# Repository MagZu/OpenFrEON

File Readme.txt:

The plan is to gradually promote adjustments:
1. Adjust the size of the buckle so that it can fit the gopro socket in the market. (Has been completed)
2. Add LeTV phone case. (During testing)
3. Adjust the structural defects of the mobile phone case. (under design)
4. Cancel the hardware. Use the wood structure to ensure the strength of the buckle. (To be started)

Shell introduction, hardware details and purchase link
http://www.openpilot.net/?thread-14.htm

In the folder
pedal
giraffe
leeco
oneplus
gopro
*old is officially owned by openfreon

All rights reserved by copyright owners

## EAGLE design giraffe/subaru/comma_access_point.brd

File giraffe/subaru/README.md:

Subaru giraffe
====

Get your panda deeper into your Subaru Impreza
May work with other cars with the same connector

====

All switching between stock ADAS on and Stock ADAS off is done via a relay

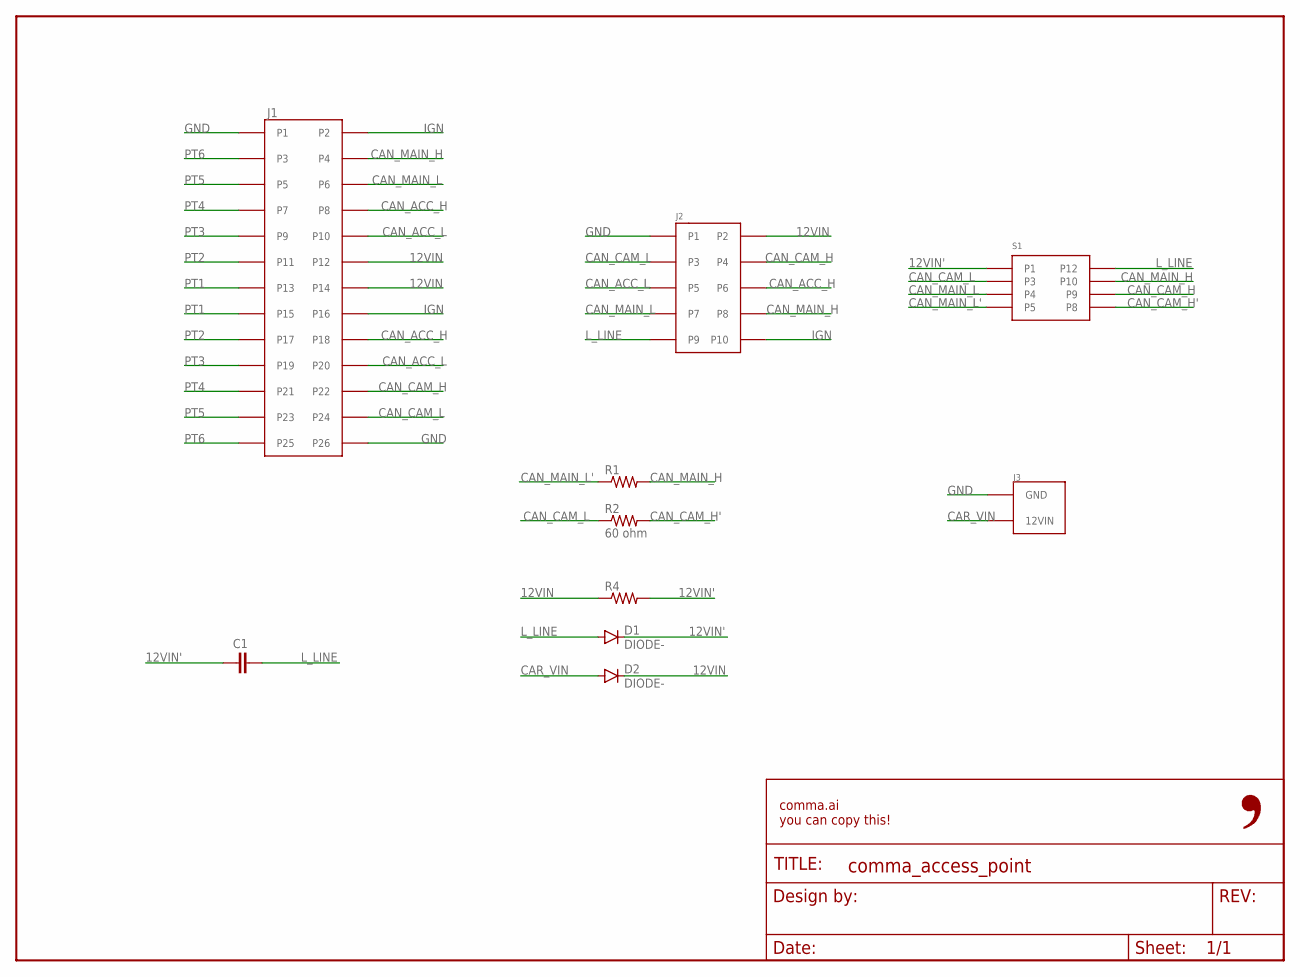
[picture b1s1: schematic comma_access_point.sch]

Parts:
C1: C0805; 0805-C
D1, D2: DIODE-; DO-214
FRAME1: FRAME-LETTER-OPENNO_PACKAGE; DUMMY
J1: 5018762640
J2: 5018761040
J3: 3-794618-2
R1, R4: R0402; 0402-R
R2: 60 ohm; 0402-R
S1: G6S-2G-DC12; G6S-26-DC12

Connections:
12VIN: D2.1 (C), J1.P12, J1.P14, J2.P2, R4.1
12VIN': C1.1, D1.1 (C), R4.2, S1.P1
CAN_ACC_H: J1.P8, J1.P18, J2.P6
CAN_ACC_L: J1.P10, J1.P20, J2.P5
CAN_CAM_H: J1.P22, J2.P4, S1.P9
CAN_CAM_H': R2.2, S1.P8
CAN_CAM_L: J1.P24, J2.P3, R2.1, S1.P3
CAN_MAIN_H: J1.P4, J2.P8, R1.2, S1.P10
CAN_MAIN_L: J1.P6, J2.P7, S1.P4
CAN_MAIN_L': R1.1, S1.P5
CAR_VIN: D2.2 (A), J3.12VIN
GND: J1.P1, J1.P26, J2.P1, J3.GND
IGN: J1.P2, J1.P16, J2.P10
L_LINE: C1.2, D1.2 (A), J2.P9, S1.P12
PT1: J1.P13, J1.P15
PT2: J1.P11, J1.P17
PT3: J1.P9, J1.P19
PT4: J1.P7, J1.P21
PT5: J1.P5, J1.P23
PT6: J1.P3, J1.P25

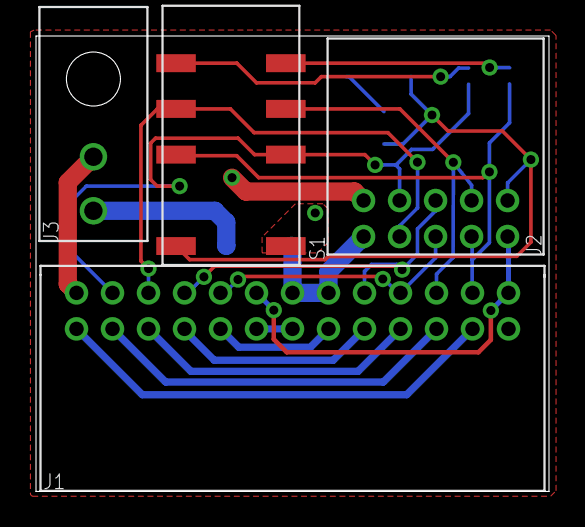
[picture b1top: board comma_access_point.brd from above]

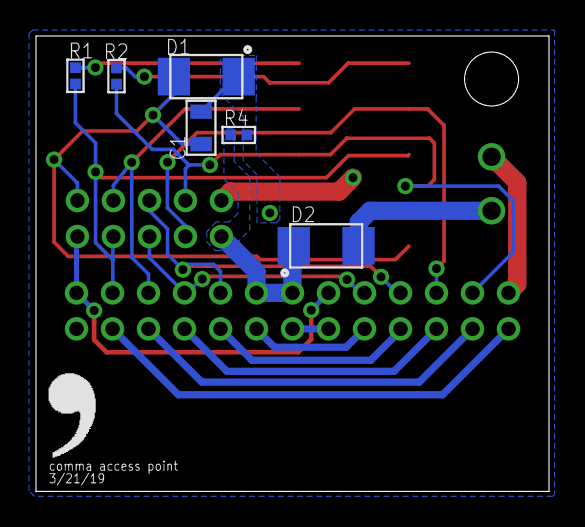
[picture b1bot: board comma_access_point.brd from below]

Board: 2 copper layers, 28.5 x 25.3 mm, 12 parts (7 on the bottom side), 20 nets.

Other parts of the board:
U$1: LOGO

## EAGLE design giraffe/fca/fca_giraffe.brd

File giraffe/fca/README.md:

FCA (Fiat Chrysler Automotive) Giraffe
====

Get your panda deeper into your:

- 2017 Chrysler Pacifica Hybrid

May fit other FCA cars as well.

The switches
====

The 2 DIP switches control signals to the stock ADAS system

- 1 -- IGN to camera

- 2 -- ADAS CAN1 -> camera CAN (OBDII pins 12 & 13)

Initial design from the community from: [@adhintz](https://github.com/adhintz)

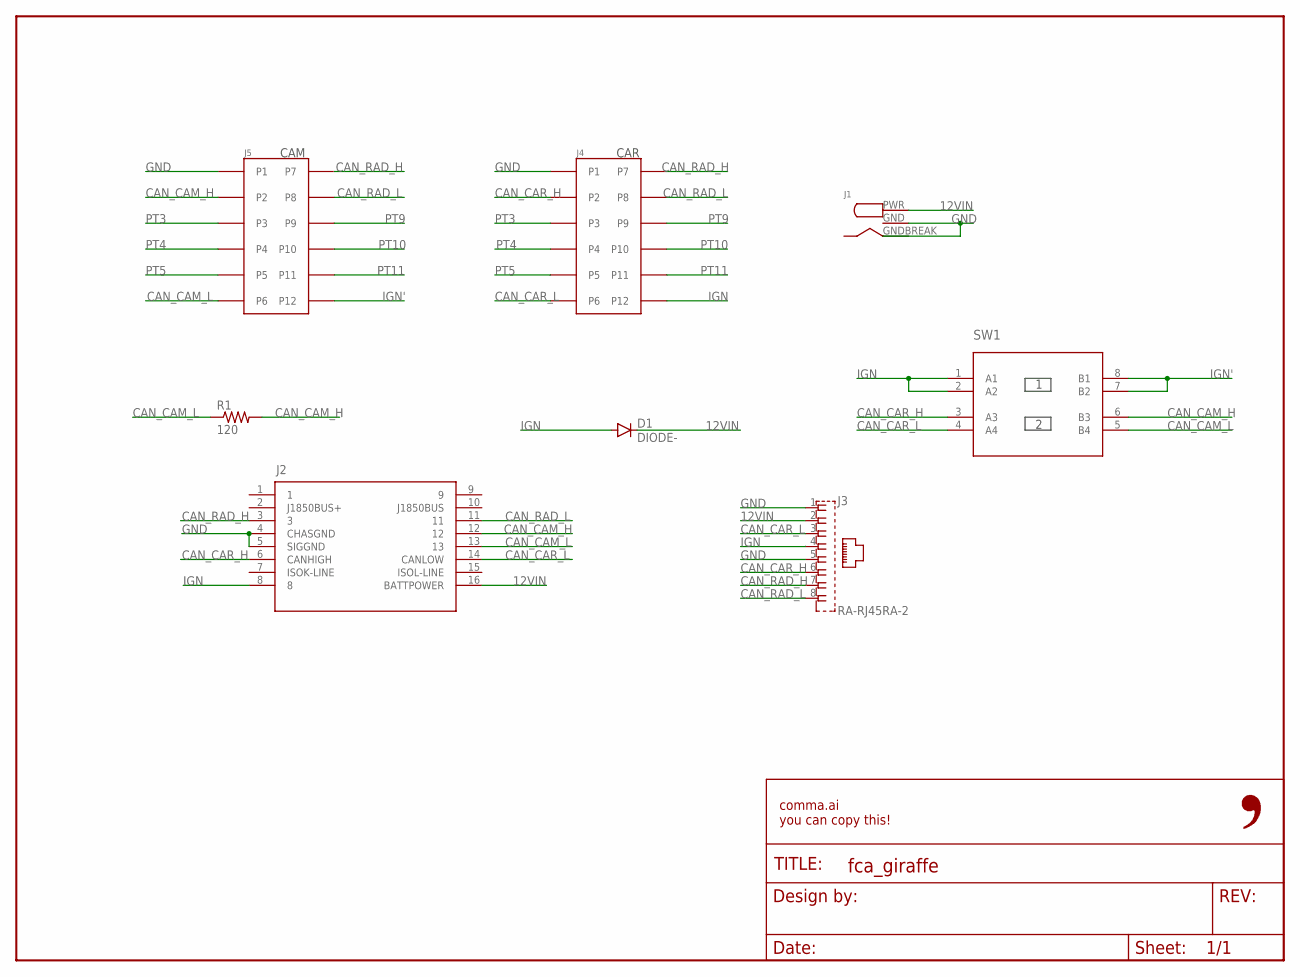
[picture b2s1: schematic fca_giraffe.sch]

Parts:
D1: DIODE-; DO-214
FRAME1: FRAME-LETTER-OPENNO_PACKAGE; DUMMY
J1: RASM722PX
J2: OBDII-FEMALE-CUT; OBDII-FEMALE-MIDCUT
J3: RA-RJ45RA-2; RA-RJ45-2
J4: 0348250124
J5: 0348240124
R1: 120; 0603-R
SW1: 2XDPST-CTS; 2-DPST

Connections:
12VIN: D1.1 (C), J1.PWR (12VIN), J2.16 (BATTPOWER), J3.2
CAN_CAM_H: J2.12, J5.P2, R1.2, SW1.6 (B3)
CAN_CAM_L: J2.13, J5.P6, R1.1, SW1.5 (B4)
CAN_CAR_H: J2.6 (CANHIGH), J3.6, J4.P2, SW1.3 (A3)
CAN_CAR_L: J2.14 (CANLOW), J3.3, J4.P6, SW1.4 (A4)
CAN_RAD_H: J2.3, J3.7, J4.P7, J5.P7
CAN_RAD_L: J2.11, J3.8, J4.P8, J5.P8
GND: J1.GND, J1.GNDBREAK, J2.4 (CHASGND), J2.5 (SIGGND), J3.1, J3.5, J4.P1, J5.P1
IGN: D1.2 (A), J2.8, J3.4, J4.P12, SW1.1 (A1), SW1.2 (A2)
IGN': J5.P12, SW1.7 (B2), SW1.8 (B1)
PT3: J4.P3, J5.P3
PT4: J4.P4, J5.P4
PT5: J4.P5, J5.P5
PT9: J4.P9, J5.P9
PT10: J4.P10, J5.P10
PT11: J4.P11, J5.P11

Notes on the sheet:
CAR
CAM

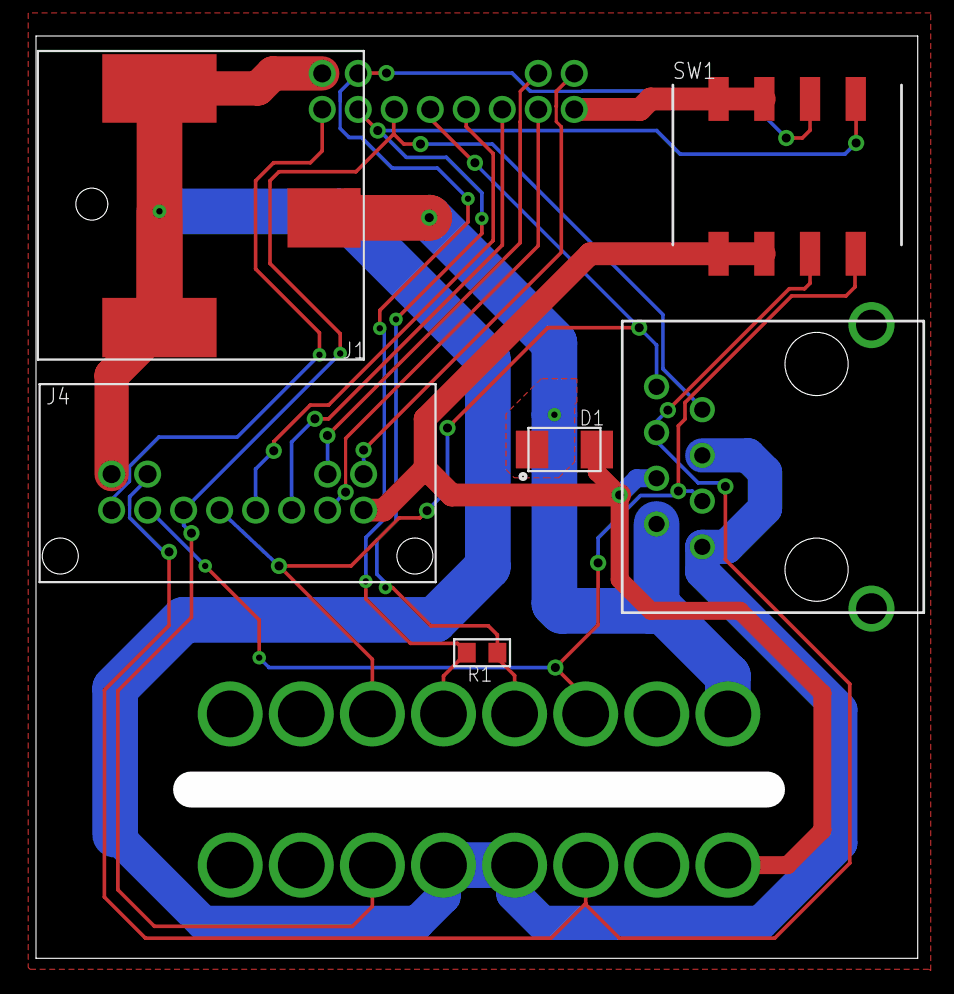
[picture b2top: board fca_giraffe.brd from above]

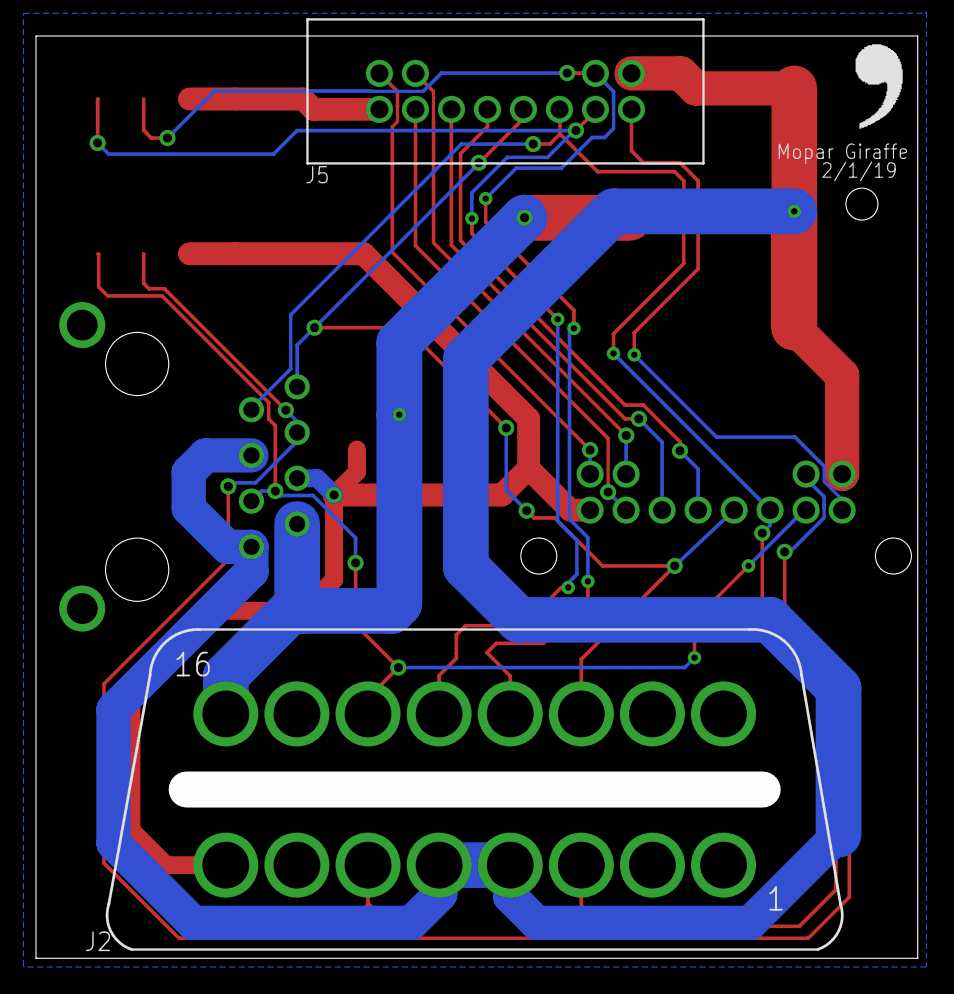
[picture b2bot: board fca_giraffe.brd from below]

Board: 2 copper layers, 49.0 x 51.2 mm, 10 parts (3 on the bottom side), 16 nets.

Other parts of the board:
U$1: LOGO

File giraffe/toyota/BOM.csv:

Ref Des,Package,Manufacturer PN,Qty,Link
J1,12-pin,1318774-1,1,http://www.mouser.com/Search/ProductDetail.aspx?R=1318774-1v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
J2,12-pin-RA,1318772-2,1,http://www.mouser.com/Search/ProductDetail.aspx?R=1318772-2v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
,,1123343-1,12,https://www.digikey.com/product-detail/en/te-connectivity-am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
,,PRPC040SAAN-RC,1,https://www.digikey.com/products/en?keywords=S1011EC-40-ND
J3,16-pin,OBDII-FEMALE,1,https://cn1514770021qfbj.en.alibaba.com/product/60598699808-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
J4,RJ45-RA,A-2004-2-4-LPS-N-R,1,https://www.digikey.com/product-detail/en/assmann-wsw-compon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
J5,3-pin,EJ508A,1,https://www.digikey.com/products/en?keywords=ej508a
SW1,SMD,204-214ST,1,https://www.digikey.com/scripts/DkSearch/dksus.dll?Detail&it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
R1,0603,ERJ-PA3F1200V,1,https://www.digikey.com/short/p47rhj
SCREWs,Phillips,92010A118,2,https://www.mcmaster.com/#catalog/92010A118

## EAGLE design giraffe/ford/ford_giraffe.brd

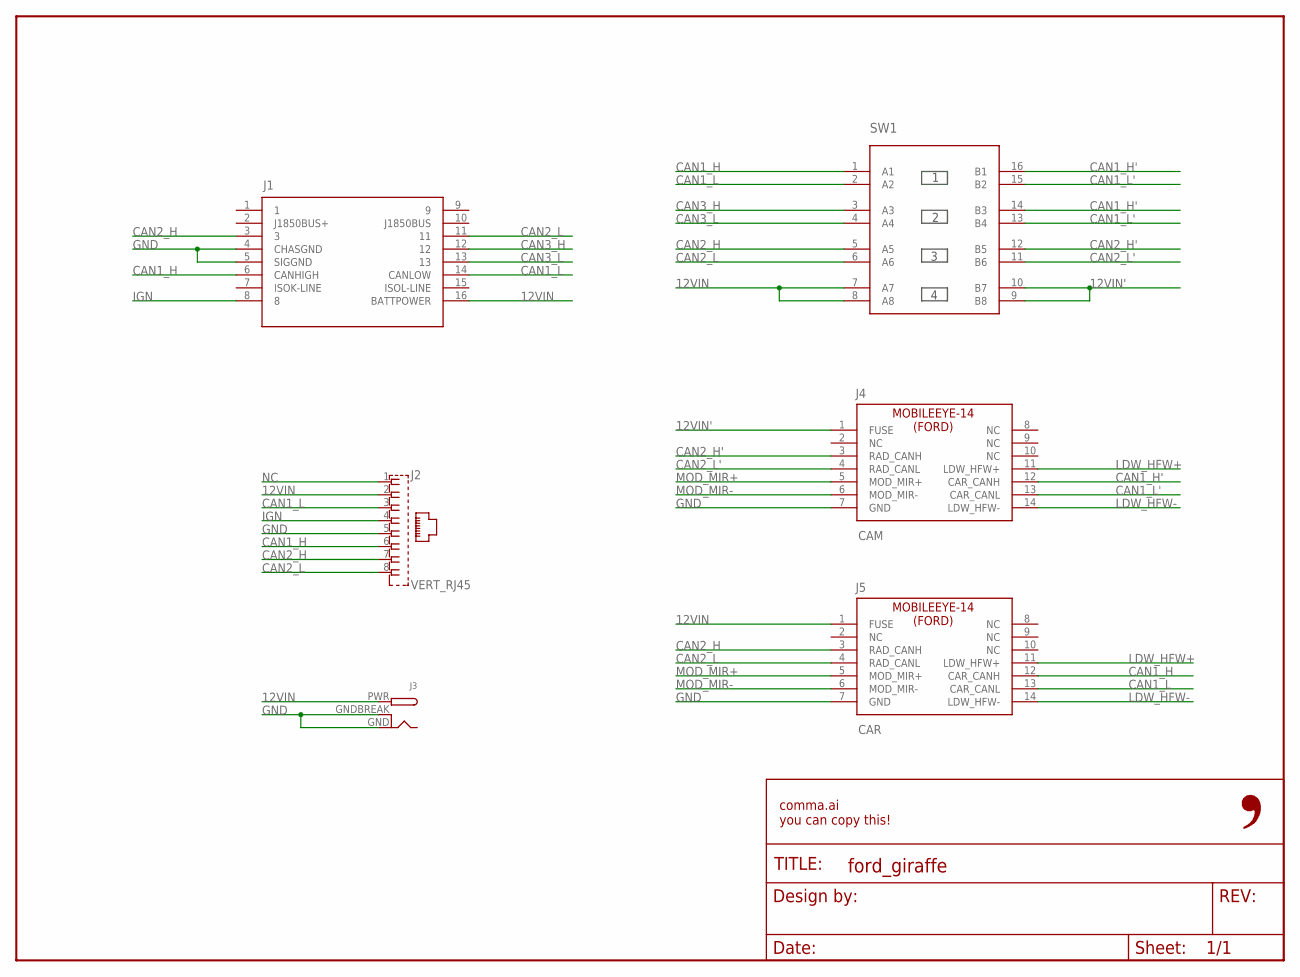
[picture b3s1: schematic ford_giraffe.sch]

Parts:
FRAME1: FRAME-LETTER-OPENNO_PACKAGE; DUMMY
J1: OBDII-FEMALE-CUT; OBDII-FEMALE-MIDCUT
J2: VERT_RJ45; GLX-S-88M
J3: DCBARRELPTH; DCJACK_2MM_PTH
J4: CAM; 2X7-FORD-CAR
J5: CAR; 2X7-FORD-CAM
SW1: 4XDPSTSMT; 4-DPST

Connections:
12VIN: J1.16 (BATTPOWER), J2.2, J3.PWR, J5.1 (FUSE), SW1.7 (A7), SW1.8 (A8)
12VIN': J4.1 (FUSE), SW1.9 (B8), SW1.10 (B7)
CAN1_H: J1.6 (CANHIGH), J2.6, J5.12 (CAR_CANH), SW1.1 (A1)
CAN1_H': J4.12 (CAR_CANH), SW1.14 (B3), SW1.16 (B1)
CAN1_L: J1.14 (CANLOW), J2.3, J5.13 (CAR_CANL), SW1.2 (A2)
CAN1_L': J4.13 (CAR_CANL), SW1.13 (B4), SW1.15 (B2)
CAN2_H: J1.3, J2.7, J5.3 (RAD_CANH), SW1.5 (A5)
CAN2_H': J4.3 (RAD_CANH), SW1.12 (B5)
CAN2_L: J1.11, J2.8, J5.4 (RAD_CANL), SW1.6 (A6)
CAN2_L': J4.4 (RAD_CANL), SW1.11 (B6)
CAN3_H: J1.12, SW1.3 (A3)
CAN3_L: J1.13, SW1.4 (A4)
GND: J1.4 (CHASGND), J1.5 (SIGGND), J2.5, J3.GND, J3.GNDBREAK, J4.7 (GND), J5.7 (GND)
IGN: J1.8, J2.4
LDW_HFW+: J4.11 (LDW_HFW+), J5.11 (LDW_HFW+)
LDW_HFW-: J4.14 (LDW_HFW-), J5.14 (LDW_HFW-)
MOD_MIR+: J4.5 (MOD_MIR+), J5.5 (MOD_MIR+)
MOD_MIR-: J4.6 (MOD_MIR-), J5.6 (MOD_MIR-)
NC: J2.1

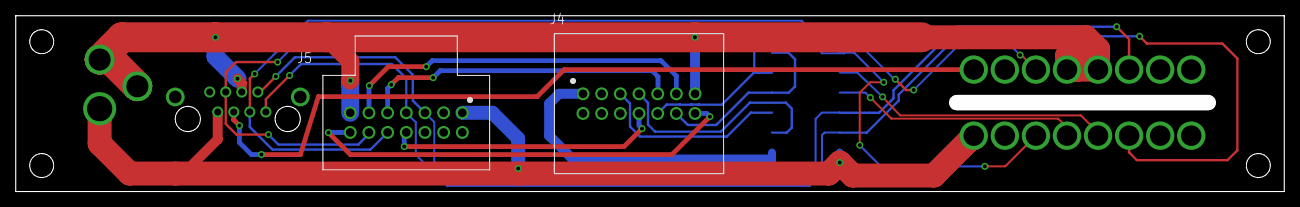
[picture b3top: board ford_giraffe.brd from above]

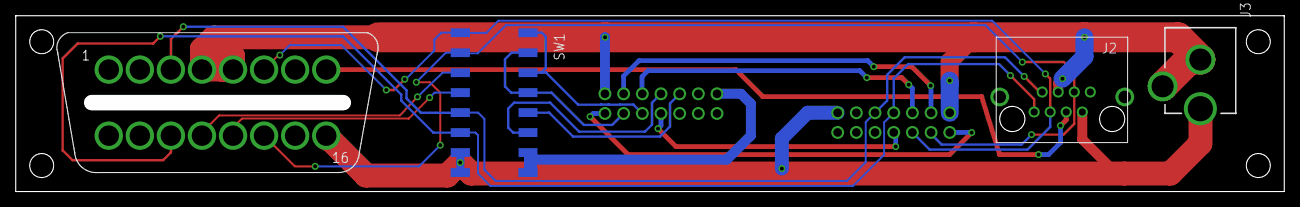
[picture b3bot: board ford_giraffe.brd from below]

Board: 2 copper layers, 161.3 x 22.4 mm, 7 parts (4 on the bottom side), 18 nets.

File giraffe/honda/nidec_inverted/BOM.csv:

Ref Des,Package,Manufacturer PN,Qty,Link
J1,20-pin-RA,MX34020NF1,1,https://www.digikey.com/product-detail/en/jae-electronics/MX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
J2,20-pin,MX34020SF1,1,https://www.digikey.com/scripts/DkSearch/dksus.dll?Detail&it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
,,M34S75C4F1,20,https://www.digikey.com/product-detail/en/jae-electronics/M3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
,,PRPC040SAAN-RC,1,https://www.digikey.com/products/en?keywords=S1011EC-40-ND
J3,16-pin,OBDII-FEMALE,1,https://cn1514770021qfbj.en.alibaba.com/product/60598699808-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
J4,RJ45-VERT,A-2014-2-4-LP/FS-R,1,https://www.digikey.com/scripts/DkSearch/dksus.dll?Detail&it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
SW1,SMD,204-214ST,1,https://www.digikey.com/scripts/DkSearch/dksus.dll?Detail&it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
SCREWs,Phillips,92010A118,2,https://www.mcmaster.com/#catalog/92010A118

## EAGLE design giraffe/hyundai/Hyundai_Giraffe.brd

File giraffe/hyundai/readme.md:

Hyundai giraffe
====

Get your panda deeper into your compatible Hyundai vehicle. Built with pinout for our Hyundai Sante Fe. May work with other Hyundai/Kia, check EWD for verification. 

The switches
====

The 4 DIP switches control signals to the stock ADAS system

- 1 -- ADAS CAN1 -> main body CAN

- 2 -- ADAS CAN1 -> panda CAN3 (OBDII pins 12 & 13)

- 3 -- IGNITION POWER -> panda power

- 4 -- ADAS power & ignition -> power & ignition

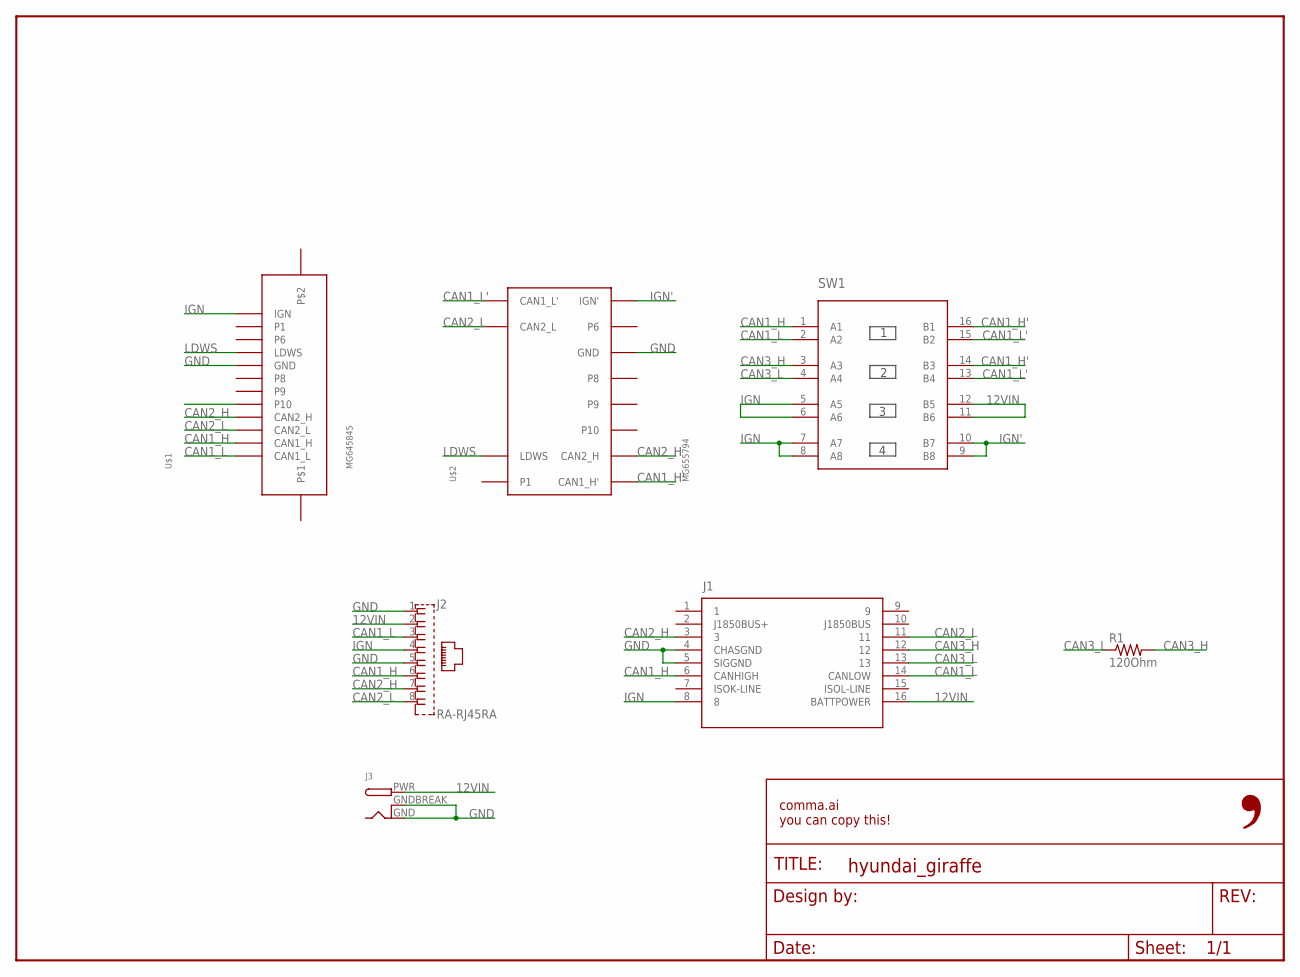
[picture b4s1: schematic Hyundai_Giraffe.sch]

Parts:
FRAME1: FRAME-LETTER-OPENNO_PACKAGE; DUMMY
J1: OBDII-FEMALE-CUT; OBDII-FEMALE-MIDCUT
J2: RA-RJ45RA; RA-RJ45
J3: DCBARRELPTH; DCJACK_2MM_PTH
R1: 120Ohm; 0603-R
SW1: 4XDPSTSMT; 4-DPST
U$1: MG645845
U$2: MG655794

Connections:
12VIN: J1.16 (BATTPOWER), J2.2, J3.PWR, SW1.11 (B6), SW1.12 (B5)
CAN1_H: J1.6 (CANHIGH), J2.6, SW1.1 (A1), U$1.CAN1_H
CAN1_H': SW1.14 (B3), SW1.16 (B1), U$2.CAN1_H'
CAN1_L: J1.14 (CANLOW), J2.3, SW1.2 (A2), U$1.CAN1_L
CAN1_L': SW1.13 (B4), SW1.15 (B2), U$2.CAN1_L'
CAN2_H: J1.3, J2.7, U$1.CAN2_H, U$2.CAN2_H
CAN2_L: J1.11, J2.8, U$1.CAN2_L, U$2.CAN2_L
CAN3_H: J1.12, R1.2, SW1.3 (A3)
CAN3_L: J1.13, R1.1, SW1.4 (A4)
GND: J1.4 (CHASGND), J1.5 (SIGGND), J2.1, J2.5, J3.GND, J3.GNDBREAK, U$1.GND, U$2.GND
IGN: J1.8, J2.4, SW1.5 (A5), SW1.6 (A6), SW1.7 (A7), SW1.8 (A8), U$1.IGN
IGN': SW1.9 (B8), SW1.10 (B7), U$2.IGN'
LDWS: U$1.LDWS, U$2.LDWS

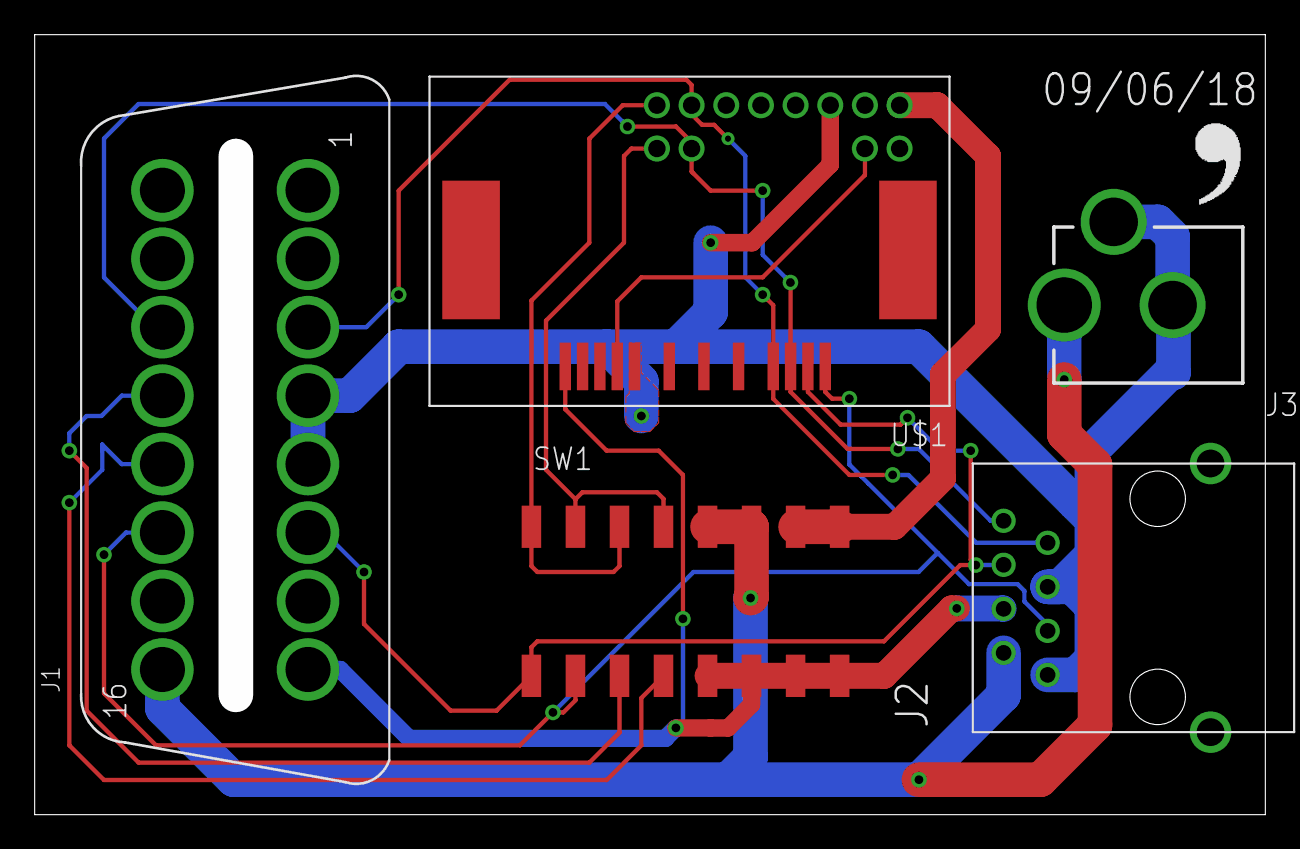
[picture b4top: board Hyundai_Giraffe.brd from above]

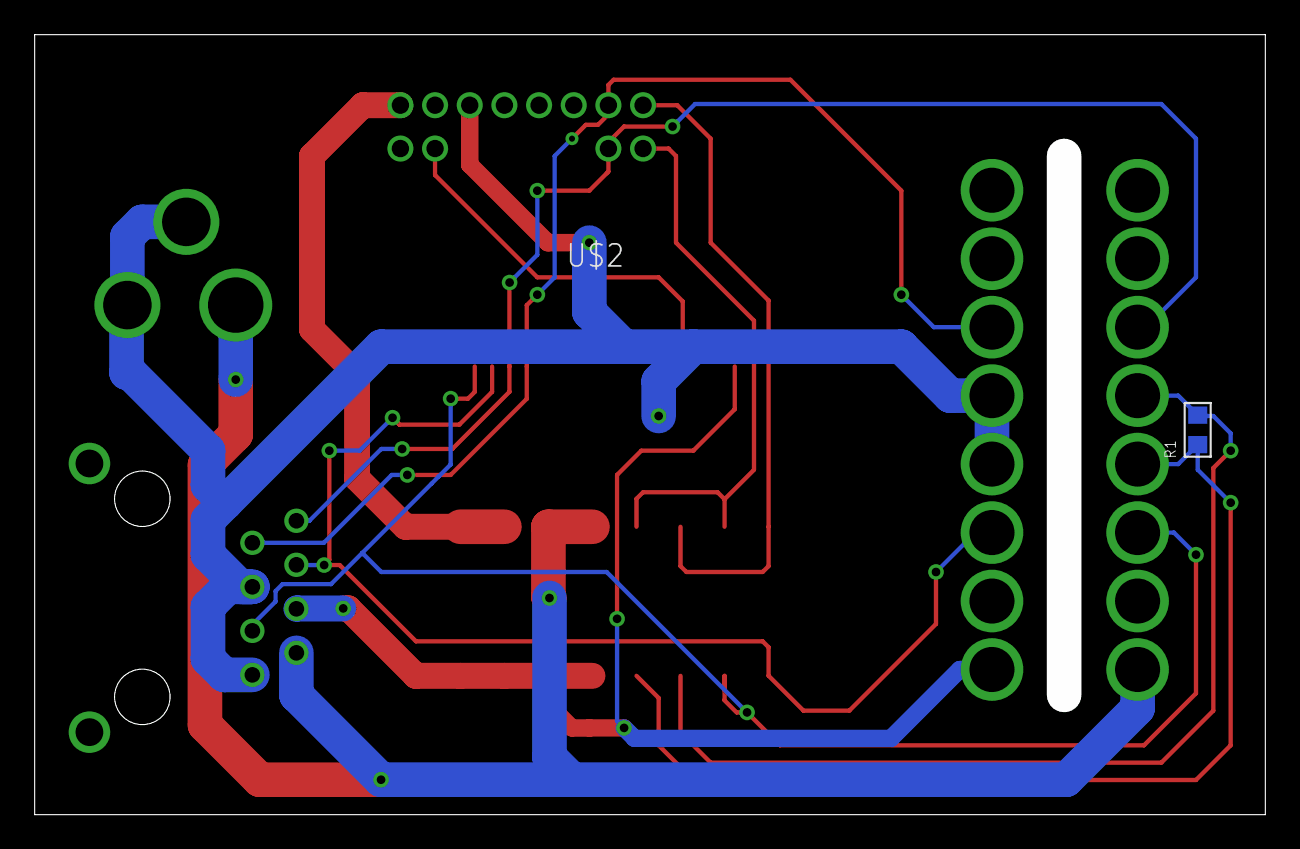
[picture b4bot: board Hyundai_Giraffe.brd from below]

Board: 2 copper layers, 71.0 x 45.0 mm, 9 parts (2 on the bottom side), 13 nets.

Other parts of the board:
U$3: LOGO

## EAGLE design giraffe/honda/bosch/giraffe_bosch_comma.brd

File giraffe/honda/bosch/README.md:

Honda giraffe (Bosch ADAS)
====

Get your panda deeper into your:

- 2017+ Honda CR-V
- 2017+ Honda Civic Hatchback
- 2018+ Honda Accord

May fit other Hondas with Bosch hardware as well.

The switches
====

The 2 DIP switches control signals to the stock ADAS system

- 1 -- IGN to camera

- 2 -- ADAS CAN2 -> camera CAN (OBDII pins 12 & 13)

Initial design from the community from: [@csouers](https://github.com/csouers), [@energee](https://github.com/energee), and Alaric Egli

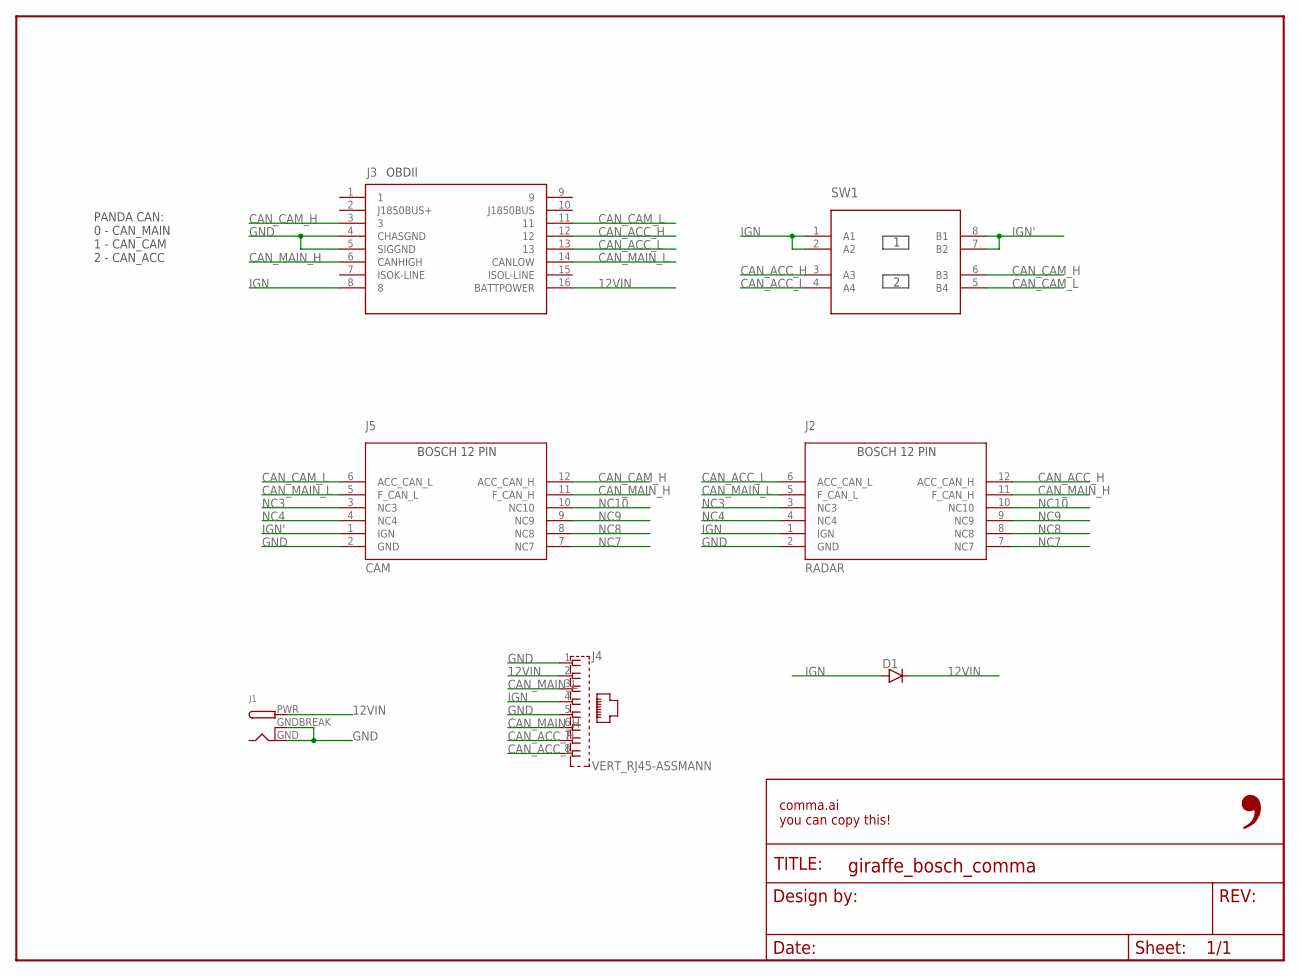
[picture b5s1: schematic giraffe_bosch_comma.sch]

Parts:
D1: DIODE-; DO-214
FRAME1: FRAME-LETTER-OPENNO_PACKAGE; DUMMY
J1: DCBARRELPTH; DCJACK_2MM_PTH
J2: RADAR; BOSCH_12_PIN_FEMALE
J3: OBDII-FEMALE-CUT; OBDII-FEMALE-MIDCUT
J4: VERT_RJ45-ASSMANN; RJ45-VERT
J5: CAM; BOSCH_12_PIN_MALE
SW1: 2XDPST-CTS; 2-DPST

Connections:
12VIN: D1.1 (C), J1.PWR, J3.16 (BATTPOWER), J4.2
CAN_ACC_H: J2.12 (ACC_CAN_H), J3.12, J4.7, SW1.3 (A3)
CAN_ACC_L: J2.6 (ACC_CAN_L), J3.13, J4.8, SW1.4 (A4)
CAN_CAM_H: J3.3, J5.12 (ACC_CAN_H), SW1.6 (B3)
CAN_CAM_L: J3.11, J5.6 (ACC_CAN_L), SW1.5 (B4)
CAN_MAIN_H: J2.11 (F_CAN_H), J3.6 (CANHIGH), J4.6, J5.11 (F_CAN_H)
CAN_MAIN_L: J2.5 (F_CAN_L), J3.14 (CANLOW), J4.3, J5.5 (F_CAN_L)
GND: J1.GND, J1.GNDBREAK, J2.2 (GND), J3.4 (CHASGND), J3.5 (SIGGND), J4.1, J4.5, J5.2 (GND)
IGN: D1.2 (A), J2.1 (IGN), J3.8, J4.4, SW1.1 (A1), SW1.2 (A2)
IGN': J5.1 (IGN), SW1.7 (B2), SW1.8 (B1)
NC3: J2.3 (NC3), J5.3 (NC3)
NC4: J2.4 (NC4), J5.4 (NC4)
NC7: J2.7 (NC7), J5.7 (NC7)
NC8: J2.8 (NC8), J5.8 (NC8)
NC9: J2.9 (NC9), J5.9 (NC9)
NC10: J2.10 (NC10), J5.10 (NC10)

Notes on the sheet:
OBDII
PANDA CAN: 0 - CAN_MAIN 1 - CAN_CAM 2 - CAN_ACC

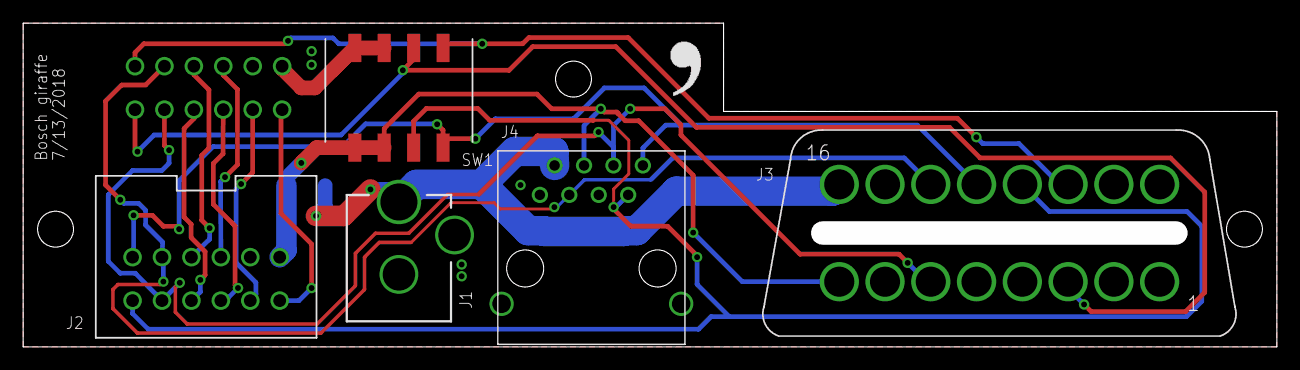
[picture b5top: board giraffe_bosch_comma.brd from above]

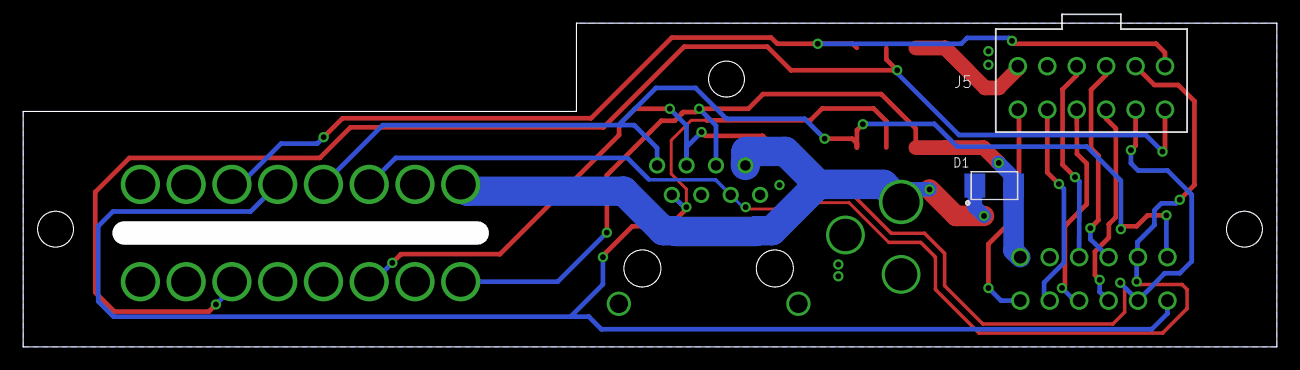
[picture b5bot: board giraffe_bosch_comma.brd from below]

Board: 2 copper layers, 108.2 x 27.9 mm, 9 parts (2 on the bottom side), 16 nets.

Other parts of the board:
U$1: LOGO

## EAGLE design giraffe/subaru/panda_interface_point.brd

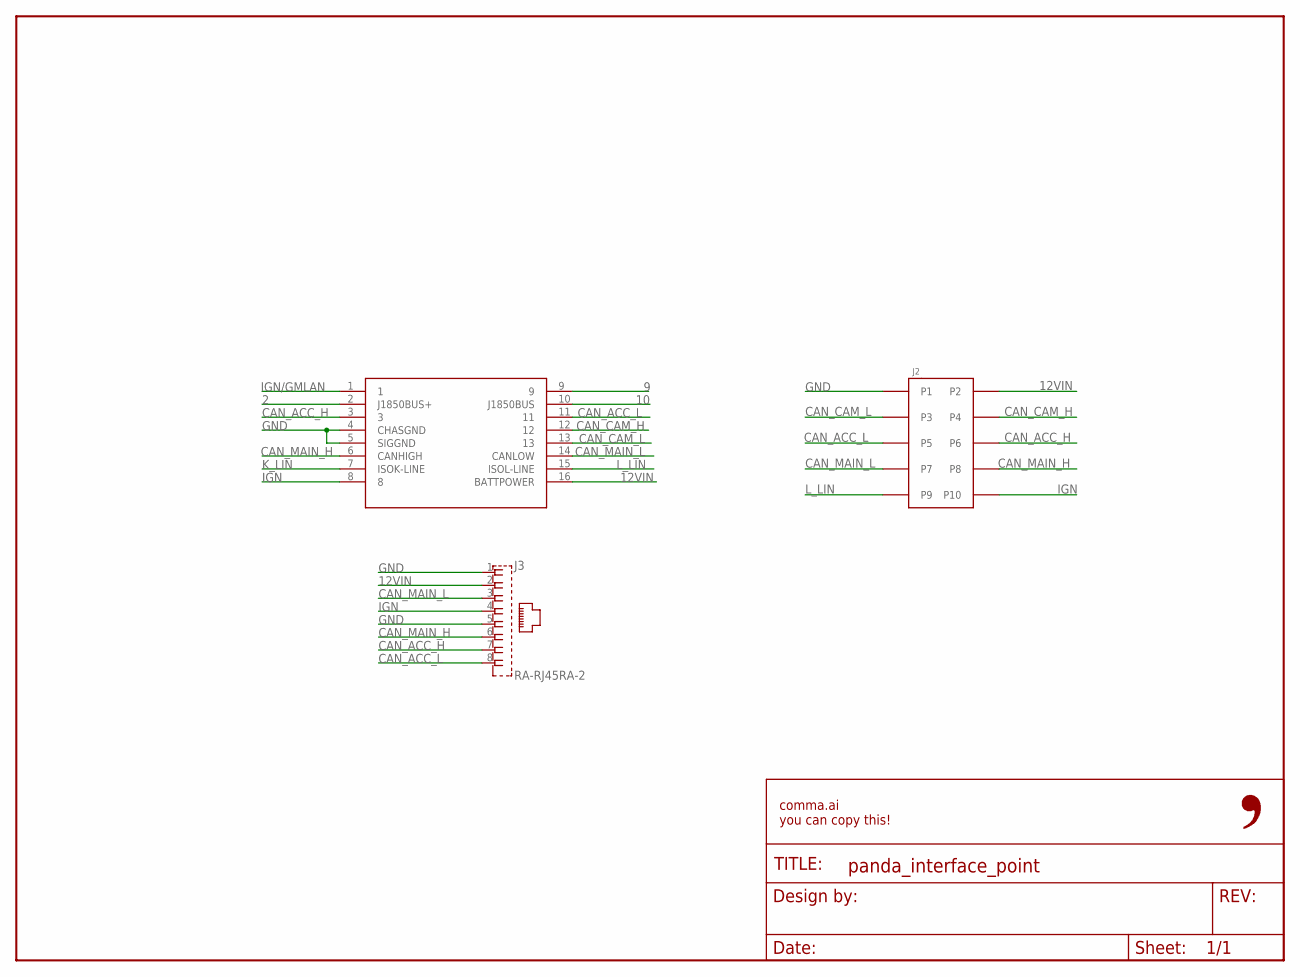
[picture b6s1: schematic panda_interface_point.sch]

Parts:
FRAME1: FRAME-LETTER-OPENNO_PACKAGE; DUMMY
J1: OBDII-FEMALE-CUT; OBDII-FEMALE-MIDCUT
J2: 5018761040
J3: RA-RJ45RA-2; RA-RJ45-2

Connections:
2: J1.2 (J1850BUS+)
9: J1.9
10: J1.10 (J1850BUS)
12VIN: J1.16 (BATTPOWER), J2.P2, J3.2
CAN_ACC_H: J1.3, J2.P6, J3.7
CAN_ACC_L: J1.11, J2.P5, J3.8
CAN_CAM_H: J1.12, J2.P4
CAN_CAM_L: J1.13, J2.P3
CAN_MAIN_H: J1.6 (CANHIGH), J2.P8, J3.6
CAN_MAIN_L: J1.14 (CANLOW), J2.P7, J3.3
GND: J1.4 (CHASGND), J1.5 (SIGGND), J2.P1, J3.1, J3.5
IGN: J1.8, J2.P10, J3.4
IGN/GMLAN: J1.1
K_LIN: J1.7 (ISOK-LINE)
L_LIN: J1.15 (ISOL-LINE), J2.P9

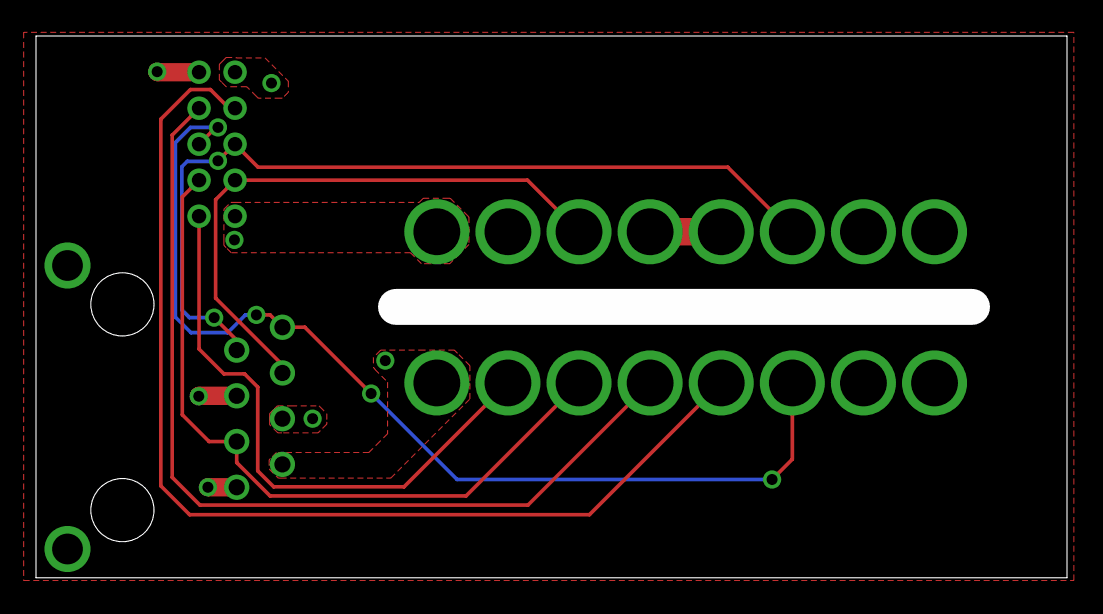
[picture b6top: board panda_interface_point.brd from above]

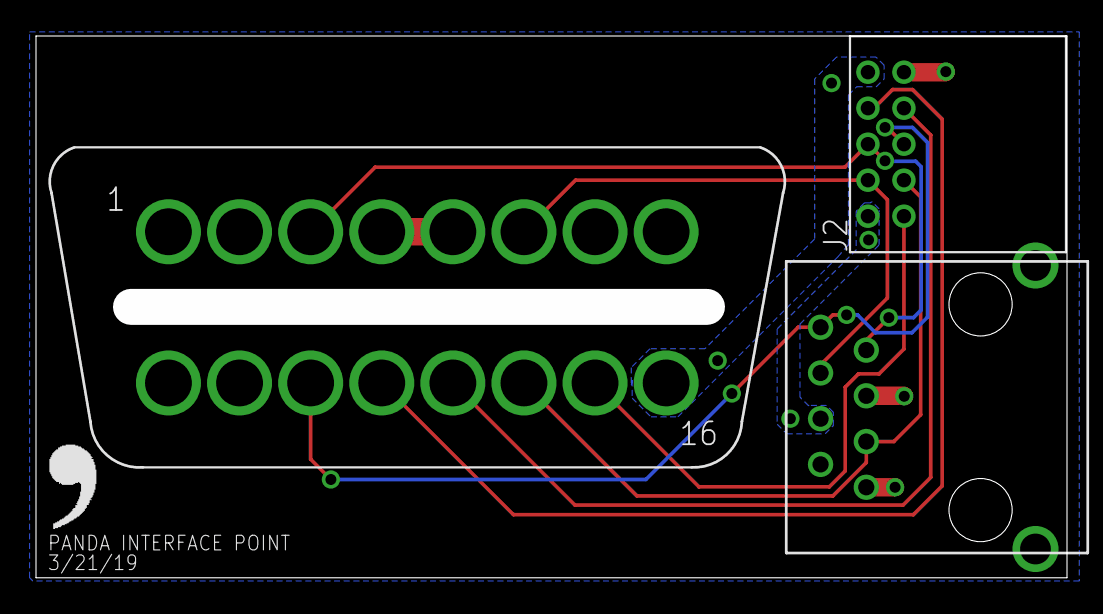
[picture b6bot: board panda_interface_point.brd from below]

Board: 2 copper layers, 57.3 x 30.1 mm, 5 parts (4 on the bottom side), 10 nets.

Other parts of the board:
U$1: LOGO

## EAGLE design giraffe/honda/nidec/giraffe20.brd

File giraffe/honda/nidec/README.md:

Honda giraffe
====

Get your panda deeper into your Honda Civic or Acura ILX

The switches
====

The 4 DIP switches control signals to the stock ADAS system

- 1 -- ADAS CAN1 -> main body CAN

- 2 -- ADAS CAN1 -> panda CAN3 (OBDII pins 12 & 13)

- 3 -- ADAS CAN2 -> radar CAN

- 4 -- ADAS power & ignition -> power & ignition

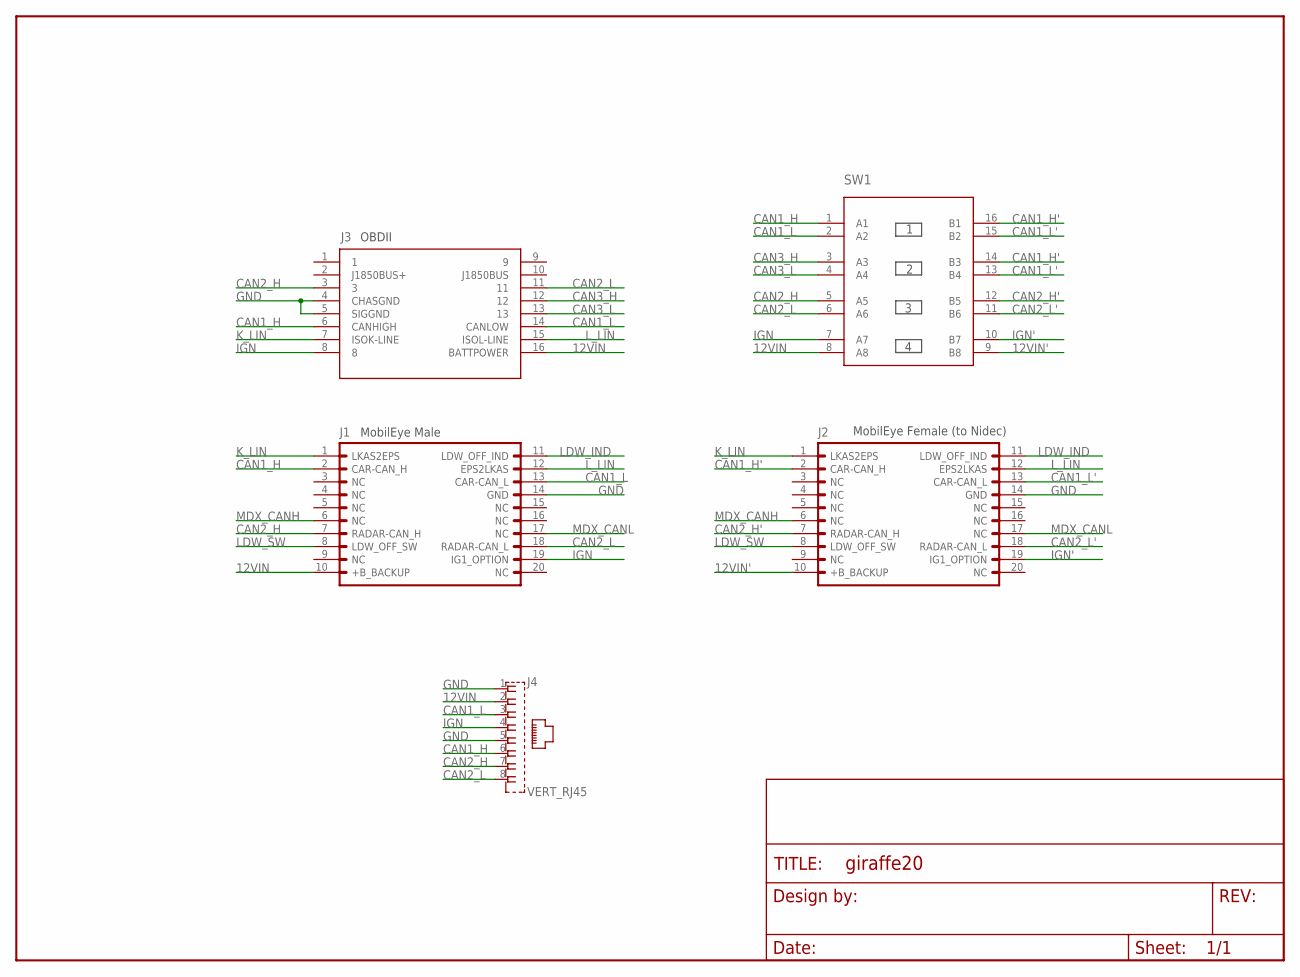
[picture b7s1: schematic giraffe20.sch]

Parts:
FRAME1: FRAME-LETTERNO_PACKAGE; DUMMY
J1: MOBILEYERAMALE; 2X10(RA)
J2: MOBILEYEFEMALE; 2X10(JAE_FEMALE)
J3: OBDII-FEMALE-CUT; OBDII-FEMALE-MIDCUT
J4: VERT_RJ45; GLX-S-88M
SW1: 4XDPSTSMT; 4-DPST

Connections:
12VIN: J1.10 (+B_BACKUP), J3.16 (BATTPOWER), J4.2, SW1.8 (A8)
12VIN': J2.10 (+B_BACKUP), SW1.9 (B8)
CAN1_H: J1.2 (CAR-CAN_H), J3.6 (CANHIGH), J4.6, SW1.1 (A1)
CAN1_H': J2.2 (CAR-CAN_H), SW1.14 (B3), SW1.16 (B1)
CAN1_L: J1.13 (CAR-CAN_L), J3.14 (CANLOW), J4.3, SW1.2 (A2)
CAN1_L': J2.13 (CAR-CAN_L), SW1.13 (B4), SW1.15 (B2)
CAN2_H: J1.7 (RADAR-CAN_H), J3.3, J4.7, SW1.5 (A5)
CAN2_H': J2.7 (RADAR-CAN_H), SW1.12 (B5)
CAN2_L: J1.18 (RADAR-CAN_L), J3.11, J4.8, SW1.6 (A6)
CAN2_L': J2.18 (RADAR-CAN_L), SW1.11 (B6)
CAN3_H: J3.12, SW1.3 (A3)
CAN3_L: J3.13, SW1.4 (A4)
GND: J1.14 (GND), J2.14 (GND), J3.4 (CHASGND), J3.5 (SIGGND), J4.1, J4.5
IGN: J1.19 (IG1_OPTION), J3.8, J4.4, SW1.7 (A7)
IGN': J2.19 (IG1_OPTION), SW1.10 (B7)
K_LIN: J1.1 (LKAS2EPS), J2.1 (LKAS2EPS), J3.7 (ISOK-LINE)
LDW_IND: J1.11 (LDW_OFF_IND), J2.11 (LDW_OFF_IND)
LDW_SW: J1.8 (LDW_OFF_SW), J2.8 (LDW_OFF_SW)
L_LIN: J1.12 (EPS2LKAS), J2.12 (EPS2LKAS), J3.15 (ISOL-LINE)
MDX_CANH: J1.6 (NC), J2.6 (NC)
MDX_CANL: J1.17 (NC), J2.17 (NC)

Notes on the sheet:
OBDII
MobilEye Male
MobilEye Female (to Nidec)

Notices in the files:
parts and their libraries:
SparkFun-Aesthetics: Licensing: Creative Commons ShareAlike 4.0 International - https://creativecommons.org/licenses/by-sa/4.0
SparkFun-Aesthetics: Released under the Creative Commons Attribution Share-Alike 4.0 License
SparkFun-Aesthetics: https://creativecommons.org/licenses/by-sa/4.0
